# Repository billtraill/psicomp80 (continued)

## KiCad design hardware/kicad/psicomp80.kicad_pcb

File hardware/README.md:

# PSI COMP 80 main board drawings

Vector drawings of the Powertran kit's main board, and a routed KiCad board. The board
gets its parts and positions from the photos of the kit sheets in `info/pictures/`
(`kit-component-layout.webp` and `kit-pcb-artwork.webp`). It gets its electrical
connections from the circuit diagrams in the Wireless World articles.

| File | What it is |
|---|---|
| `psicomp80_pcb_routed.svg` | **The electrically accurate artwork.** The board routed from the netlist transcribed from the article circuit diagrams, drawn like the kit sheet and seen from the component side: blue is the component (top) side, red the solder (bottom) side. |
| `psicomp80_component_layout.svg` | The component layout sheet, redrawn: board outline, section boundaries, every IC with its number and type, the discrete parts as drawn on the kit sheet, and the keyboard legends. |
| `psicomp80_pcb_artwork.svg` | The kit's original copper artwork, traced from the photo (approximate), with the pads and legends redrawn on top. |
| `kicad/psicomp80.kicad_pro`, `kicad/psicomp80.kicad_pcb` | A KiCad 10 project. Every part sits on a standard footprint with its nets, and the board is routed on two layers. The traced original copper stays on two user layers, **Artwork.Blue.Top** and **Artwork.Red.Bottom**, for comparison. |
| `kicad/PSI_COMP80.pretty`, `kicad/fp-lib-table` | The project library: the two-pad key switch footprint and the wiring-pad footprints. |
| `tools/netlist/` | The netlist, one file per article figure, plus the merged `psicomp80_netlist.json`. Its README covers sources, conventions and the points where a figure had to be interpreted. |
| `../hardware.html` | A web page of the board: zoom and pan, each side's copper on and off (routed or traced kit artwork), click a part or track for its pins and signal, the circuits talked through, and the parts list. `tools/make_hardware_page.py` makes it from the KiCad board and the netlist, with `tools/hardware_template.html`; it needs only Python 3. |

The board is 16 in × 12 in between the crop marks on the artwork. The scale comes from
the 0.1 in DIP pad pitch. The board is double-sided. On the kit's artwork the "1" mark
and the "COMPONENT SIDE" legend are printed in blue, and the "2" mark is red and reads
mirrored. So blue is the component side and red the solder side.

## How accurate it is

- **Connections** follow the article circuit diagrams pin by pin. Some figures don't
  print every pin number, and the keyboard encoder isn't drawn at all; the netlist
  README lists each case.
- **The routed tracks are not the original tracks.** Electrically they match the
  article, but the track paths don't follow the 1979 artwork. The 21L02 RAM columns are
  the exception: `make_kicad.py` pre-routes their buses itself on the component side,
  the way the original artwork does, and Freerouting routes everything else.
- **Design checks.** KiCad's DRC on the routed board finds 0 unconnected pads, and no
  clearance violations or shorts. Tracks are 0.25 mm with 0.2 mm clearance; power nets
  are 0.6 mm. Freerouting necks a few tracks down to 0.125–0.19 mm between pads. The
  remaining DRC messages are cosmetic: silkscreen overlaps, and courtyard overlaps
  where the kit sheet packs parts tightly. The "library not included" warnings go away
  once KiCad's default footprint libraries are set up.
- **IC positions** match the kit sheet. The two photos register onto each other to
  within a few hundredths of an inch, and every IC is snapped to the 0.1 in grid. IC
  types follow the article where the photo was hard to read; see `NOTES` in
  `tools/board_data.py`.
- **Discrete parts** sit at their kit-sheet position when the kit sheet shows the same
  reference, such as R40, C14, TR9 or VR1. Otherwise they go in the nearest free spot,
  in their own section of the board, to the pins they connect to.
- **The traced original copper** is approximate. The artwork photo only resolves about
  65 pixels per inch, so where tracks run close together they merge. A flat 600 dpi
  scan of the artwork sheet would make it close to track-accurate: change the corners
  in `tools/trace_artwork.py` and re-run it.

## The expansion plug

The articles never print J1's pinout, so `tools/netlist/net_board.json` gives it one. Odd pins
are the row nearer the middle of the board.

| Pins | Signals |
|---|---|
| 2, 21, 22, 31, 32, 47, 48 | 0 V |
| 4, 63, 64 | +5 V |
| 5–20 | A0–A15, straight from the Z80 |
| 23–30 | D0–D7, the buffered side of IC9–IC12 |
| 33–46 | RD, WR, MREQ, IORQ, M1, RFSH, MEM_MREQ (the IC17 side of LK3), HALT, WAIT/BUSRQ, BUSAK, INT, NMI, RESET, 2 MHz clock |
| 49–54 | IC2's spare outputs: OUT 00, 80, 40, C0, A0, E0 |
| 55–59 | IC3's spare outputs: IN 04, 02, 06, 05, 07 |
| 60, 61, 62 | +12 V, −5 V, −12 V |
| 1, 3 | not connected |

`tools/wire_expansion.py` put these nets on the routed board, and `route_board.py --keep`
routed them without disturbing the tracks already there. `tools/finish_routes.py` routed
the last six, which Freerouting couldn't fit, on a 0.1–0.2 mm grid.

## Regenerating

The scripts are in `tools/`:

| Step | Script | Runs under |
|---|---|---|
| 1 | `merge_netlist.py`: merges `netlist/net_*.json` and reports dangling nets | any Python 3 |
| 2 | `make_kicad.py`: builds the board, placing parts and putting nets on pads | KiCad's Python |
| 3 | `route_board.py`: routes the board with Freerouting (needs Java) | KiCad's Python |
| 4 | `export_routed_svg.py`: writes `psicomp80_pcb_routed.svg` | KiCad's Python |
| – | `make_drawings.py`: writes the component layout and traced artwork SVGs | any Python 3 |
| – | `trace_artwork.py`: traces the copper out of the photo (only if the photo changes) | numpy, OpenCV, Pillow, potrace |

`board_data.py` holds every placement read from the photos. Edit it to move a part.

```bash
cd hardware/tools && python3 merge_netlist.py
```

```bash
cd hardware/tools && /Applications/KiCad/KiCad.app/Contents/Frameworks/Python.framework/Versions/Current/bin/python3 make_kicad.py
```

```bash
cd hardware/tools && /Applications/KiCad/KiCad.app/Contents/Frameworks/Python.framework/Versions/Current/bin/python3 route_board.py --freerouting freerouting-2.5.0.jar --java /opt/homebrew/opt/openjdk/bin/java
```

```bash
cd hardware/tools && /Applications/KiCad/KiCad.app/Contents/Frameworks/Python.framework/Versions/Current/bin/python3 export_routed_svg.py
```

To route only what's new, keeping the existing tracks, add `--keep` to `route_board.py`; then
route anything left over with the grid router:

```bash
cd hardware/tools && /Applications/KiCad/KiCad.app/Contents/Frameworks/Python.framework/Versions/Current/bin/python3 finish_routes.py
```

Freerouting comes from https://github.com/freerouting/freerouting/releases, and Java
from `brew install openjdk`.

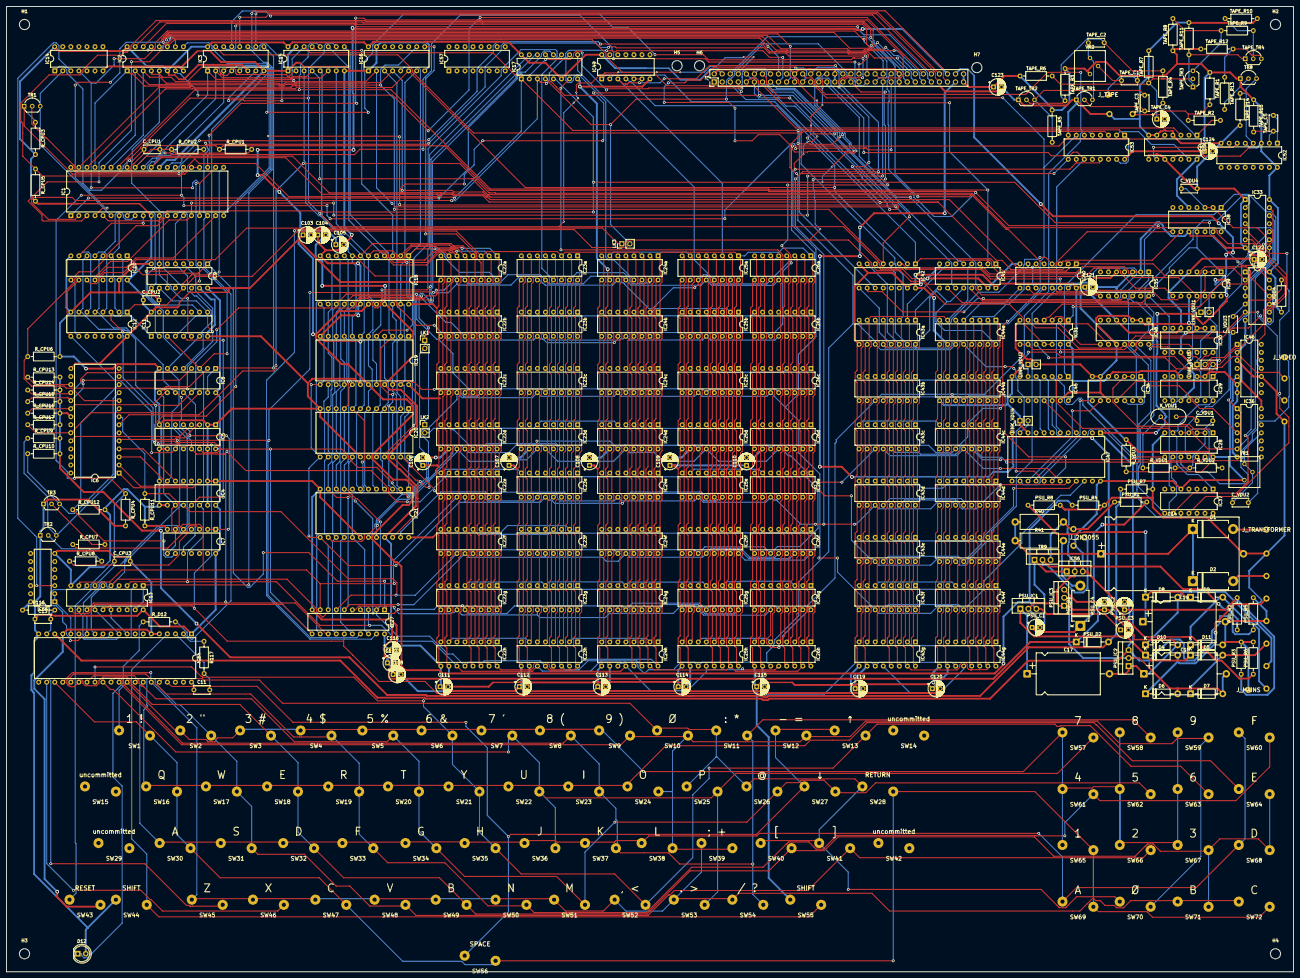
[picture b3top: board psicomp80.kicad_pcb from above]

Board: 2 copper layers, 406.4 x 304.8 mm, 316 parts (0 on the bottom side), 269 nets.

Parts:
C11: 56p; C_Disc_D5.0mm_W2.5mm_P5.00mm
C13: 22n; C_Disc_D5.0mm_W2.5mm_P5.00mm
C14: 4700u 25V; CP_Axial_L42.0mm_D23.0mm_P45.00mm_Horizontal
C17, C18: 1000u 25V; CP_Axial_L20.0mm_D13.0mm_P26.00mm_Horizontal
C19: 220u 100V; CP_Axial_L20.0mm_D13.0mm_P26.00mm_Horizontal
C103, C104, C105, C106, C107, C108, C109, C110, C111, C112, C113, C114, C115, C116, C117, C118: 100n tantalum; CP_Radial_D5.0mm_P2.50mm
C119, C120, C121, C122, C123, C124: 1u; CP_Radial_D5.0mm_P2.50mm
C_CPU1: 33p; C_Disc_D5.0mm_W2.5mm_P5.00mm
C_CPU2, C_CPU3: 100n; C_Disc_D5.0mm_W2.5mm_P5.00mm
C_VDU1: 22p; C_Disc_D5.0mm_W2.5mm_P5.00mm
C_VDU2: 220n; C_Disc_D5.0mm_W2.5mm_P5.00mm
C_VDU3: 100n; C_Disc_D5.0mm_W2.5mm_P5.00mm
C_VDU4: 200p; C_Disc_D5.0mm_W2.5mm_P5.00mm
D1, D2: 1N5401; D_DO-201AD_P12.70mm_Horizontal
D4, D5, D6, D7, D8, D9, D10, D11: 1N4002; D_DO-41_SOD81_P10.16mm_Horizontal
D12: LED (TIL209 in article); LED_D5.0mm
H1, H2, H3, H4, H5, H6, H7: MountingHole; MountingHole_3.2mm_M3
IC1: Z80; DIP-40_W15.24mm
IC2, IC3, IC17: 74LS138; DIP-16_W7.62mm
IC4, IC5: 74C173; DIP-16_W7.62mm
IC6: MM57109; DIP-28_W15.24mm
IC7: 4011; DIP-14_W7.62mm
IC8, IC9, IC10, IC11, IC12, IC15, IC16, IC53: 74LS367; DIP-16_W7.62mm
IC13, IC27: 81LS95; DIP-20_W7.62mm
IC14, IC28: 74LS04; DIP-14_W7.62mm
IC18, IC19, IC20, IC21: 2708; DIP-24_W15.24mm
IC22a, IC22b, IC22c, IC22d, IC22e, IC22f, IC22g, IC22h, IC23a, IC23b, IC23c, IC23d, IC23e, IC23f, IC23g, IC23h, IC24a, IC24b, IC24c, IC24d, IC24e, IC24f, IC24g, IC24h, IC25a, IC25b, IC25c, IC25d, IC25e, IC25f, IC25g, IC25h, IC26a, IC26b, IC26c, IC26d, IC26e, IC26f, IC26g, IC26h, IC43a, IC43b, IC43c, IC43d, IC43e, IC43f, IC43g, IC44a, IC44b, IC44c, IC44d, IC44e, IC44f, IC44g: 21L02; DIP-16_W7.62mm
IC29, IC30, IC35, IC38, IC39, IC48: 7493; DIP-14_W7.62mm
IC31, IC49: 74LS02; DIP-14_W7.62mm
IC32, IC55: 74LS00; DIP-14_W7.62mm
IC33: 7425; DIP-14_W7.62mm
IC34, IC46: 7490; DIP-14_W7.62mm
IC36: 74121; DIP-14_W7.62mm
IC37: 7492; DIP-14_W7.62mm
IC40, IC41, IC42: 74LS157; DIP-16_W7.62mm
IC45: 74165; DIP-16_W7.62mm
IC47: 2513; DIP-24_W15.24mm
IC51: 4013; DIP-14_W7.62mm
IC52: 4528; DIP-16_W7.62mm
IC54: AY-5-2376; DIP-40_W15.24mm
IC56: 7805; TO-220-3_Vertical
IC57: 74LS139; DIP-16_W7.62mm
J1: EXPANSION PLUG; PinHeader_2x32_P2.54mm_Vertical
J_2N3055: 2N3055 on heatsink (off-board); Pads_2N3055
J_MAINS: mains input (off-board); Pads_MAINS
J_TAPE: tape connections; Pads_TAPE
J_TRANSFORMER: mains transformer secondaries (off-board); Pads_TRANSFORMER
J_VIDEO: video / sync output pads; Pads_VIDEO
LINK_VDU1: Link; PinHeader_1x02_P2.54mm_Vertical
LINK_VDU2, LINK_VDU4: link (fitted for ASCII); PinHeader_1x02_P2.54mm_Vertical
LINK_VDU3: link: IC29 pin 12 or pin 14; PinHeader_1x03_P2.54mm_Vertical
LK1: wire link (normally NOT fitted); PinHeader_1x02_P2.54mm_Vertical
LK2, LK3: wire link (normally fitted); PinHeader_1x02_P2.54mm_Vertical
PSU_C1: 8u; CP_Radial_D5.0mm_P2.50mm
PSU_C2: 4u7 tantalum; CP_Radial_D5.0mm_P2.50mm
PSU_C3, PSU_C4: 1u tantalum; CP_Radial_D5.0mm_P2.50mm
PSU_D1: 1N5401; D_DO-201AD_P12.70mm_Horizontal
PSU_D2: 1N4001; D_DO-41_SOD81_P10.16mm_Horizontal
PSU_IC1: 7812; TO-220-3_Vertical
PSU_IC2: 7912; TO-220-3_Vertical
PSU_IC3: 7905; TO-220-3_Vertical
PSU_R1, PSU_R2: 100; R_Axial_DIN0207_L6.3mm_D2.5mm_P10.16mm_Horizontal
PSU_R3, PSU_R4, PSU_R5, PSU_R6, PSU_R7: 1k; R_Axial_DIN0207_L6.3mm_D2.5mm_P10.16mm_Horizontal
PSU_R8: 4k7; R_Axial_DIN0207_L6.3mm_D2.5mm_P10.16mm_Horizontal
R40: 0R22; R_Axial_DIN0414_L11.9mm_D4.5mm_P15.24mm_Horizontal
R41: 0R56; R_Axial_DIN0414_L11.9mm_D4.5mm_P15.24mm_Horizontal
R116: 680k (datasheet; kit label unreadable, possibly "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; R_Axial_DIN0207_L6.3mm_D2.5mm_P10.16mm_Horizontal
R117: ? (datasheet 100k; ~47-56k would give ~50kHz with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; R_Axial_DIN0207_L6.3mm_D2.5mm_P10.16mm_Horizontal
R_CPU1: 220; R_Axial_DIN0207_L6.3mm_D2.5mm_P10.16mm_Horizontal
R_CPU2: 1k2; R_Axial_DIN0207_L6.3mm_D2.5mm_P10.16mm_Horizontal
R_CPU3: 10R; R_Axial_DIN0207_L6.3mm_D2.5mm_P10.16mm_Horizontal
R_CPU4, R_CPU5, R_CPU7, R_CPU8, R_CPU9, R_CPU10: 47k; R_Axial_DIN0207_L6.3mm_D2.5mm_P10.16mm_Horizontal
R_CPU6, R_CPU11, R_CPU12, R_CPU13, R_CPU14, R_CPU15, R_CPU16, R_CPU17: 10k; R_Axial_DIN0207_L6.3mm_D2.5mm_P10.16mm_Horizontal
R_D12: 560R; R_Axial_DIN0207_L6.3mm_D2.5mm_P10.16mm_Horizontal
R_VDU1, R_VDU2: 470; R_Axial_DIN0207_L6.3mm_D2.5mm_P10.16mm_Horizontal
R_VDU3: 10k; R_Axial_DIN0207_L6.3mm_D2.5mm_P10.16mm_Horizontal
R_VDU4: 2k7; R_Axial_DIN0207_L6.3mm_D2.5mm_P10.16mm_Horizontal
SW1: 1 !; KeySwitch_2pad
SW2: 2 "; KeySwitch_2pad
SW3: 3 #; KeySwitch_2pad
SW4: 4 $; KeySwitch_2pad
SW5: 5 %; KeySwitch_2pad
SW6: 6 &; KeySwitch_2pad
SW7: 7 '; KeySwitch_2pad
SW8: 8 (; KeySwitch_2pad
SW9: 9 ); KeySwitch_2pad
SW10, SW70: Ø; KeySwitch_2pad
SW11: : *; KeySwitch_2pad
SW12: - =; KeySwitch_2pad
SW13: ↑; KeySwitch_2pad
SW14, SW15, SW29, SW42: uncommitted; KeySwitch_2pad
SW16: Q; KeySwitch_2pad
SW17: W; KeySwitch_2pad
SW18, SW64: E; KeySwitch_2pad
SW19: R; KeySwitch_2pad
SW20: T; KeySwitch_2pad
SW21: Y; KeySwitch_2pad
SW22: U; KeySwitch_2pad
SW23: I; KeySwitch_2pad
SW24: O; KeySwitch_2pad
SW25: P; KeySwitch_2pad
SW26: @; KeySwitch_2pad
SW27: ↓; KeySwitch_2pad
SW28: RETURN; KeySwitch_2pad
SW30, SW69: A; KeySwitch_2pad
SW31: S; KeySwitch_2pad
SW32, SW68: D; KeySwitch_2pad
SW33, SW60: F; KeySwitch_2pad
SW34: G; KeySwitch_2pad
SW35: H; KeySwitch_2pad
SW36: J; KeySwitch_2pad
SW37: K; KeySwitch_2pad
SW38: L; KeySwitch_2pad
SW39: ; +; KeySwitch_2pad
SW40: [; KeySwitch_2pad
SW41: ]; KeySwitch_2pad
SW43: RESET; KeySwitch_2pad
SW44, SW55: SHIFT; KeySwitch_2pad
SW45: Z; KeySwitch_2pad
SW46: X; KeySwitch_2pad
SW47, SW72: C; KeySwitch_2pad
SW48: V; KeySwitch_2pad
SW49, SW71: B; KeySwitch_2pad
SW50: N; KeySwitch_2pad
SW51: M; KeySwitch_2pad
SW52: , <; KeySwitch_2pad
SW53: . >; KeySwitch_2pad
SW54: / ?; KeySwitch_2pad
SW56: SPACE; KeySwitch_2pad
SW57: 7; KeySwitch_2pad
SW58: 8; KeySwitch_2pad
SW59: 9; KeySwitch_2pad
SW61: 4; KeySwitch_2pad
SW62: 5; KeySwitch_2pad
SW63: 6; KeySwitch_2pad
SW65: 1; KeySwitch_2pad
SW66: 2; KeySwitch_2pad
SW67: 3; KeySwitch_2pad
TAPE_C1, TAPE_C5: 100n; C_Disc_D5.0mm_W2.5mm_P5.00mm
TAPE_C2, TAPE_C3: 10n; C_Disc_D5.0mm_W2.5mm_P5.00mm
TAPE_C4: 10u; CP_Radial_D5.0mm_P2.50mm
TAPE_R1, TAPE_R3: 75k; R_Axial_DIN0207_L6.3mm_D2.5mm_P10.16mm_Horizontal
TAPE_R2, TAPE_R4: 56k; R_Axial_DIN0207_L6.3mm_D2.5mm_P10.16mm_Horizontal
TAPE_R5, TAPE_R9, TAPE_R10: 4k7; R_Axial_DIN0207_L6.3mm_D2.5mm_P10.16mm_Horizontal
TAPE_R6, TAPE_R7: 6k8; R_Axial_DIN0207_L6.3mm_D2.5mm_P10.16mm_Horizontal
TAPE_R8: 220; R_Axial_DIN0207_L6.3mm_D2.5mm_P10.16mm_Horizontal
TAPE_R11: 2k2; R_Axial_DIN0207_L6.3mm_D2.5mm_P10.16mm_Horizontal
TAPE_R12, TAPE_R13, TAPE_R14: 1k; R_Axial_DIN0207_L6.3mm_D2.5mm_P10.16mm_Horizontal
TAPE_R15: 27k; R_Axial_DIN0207_L6.3mm_D2.5mm_P10.16mm_Horizontal
TAPE_TR1, TAPE_TR2, TAPE_TR3, TAPE_TR4: 2N3904; TO-92_Inline_Wide
TR1, TR2, TR3, TR8: 2N3906; TO-92_Inline_Wide
TR9: TIP30; TO-220-3_Vertical
VR1: 20k multiturn; Potentiometer_Bourns_3386P_Vertical
VR2: 5k preset; Potentiometer_Bourns_3386P_Vertical
X_VDU1: 8MHz crystal; Crystal_HC49-U_Vertical

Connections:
+5V: C13.1, C103.1, C106.1, C107.1, C108.1, C109.1, C110.1, C111.1, C112.1, C113.1, C114.1, C115.1, C116.1, C119.1, C120.1, C121.1, C122.1, C123.1, C124.1, C_CPU2.1, D12.2, IC1.11, IC2.6, IC2.16, IC3.6, IC3.16, IC4.16, IC5.16, IC6.15, IC7.14, IC8.16, IC9.16, IC10.16, IC11.16, IC12.16, IC13.20, IC14.14, IC15.16, IC16.16, IC17.6, IC17.16, IC18.24, IC19.24, IC20.24, IC21.24, IC22a.9, IC22b.9, IC22c.9, IC22d.9, IC22e.9, IC22f.9, IC22g.9, IC22h.9, IC23a.9, IC23b.9, IC23c.9, IC23d.9, IC23e.9, IC23f.9, IC23g.9, IC23h.9, IC24a.9, IC24b.9, IC24c.9, IC24d.9, IC24e.9, IC24f.9, IC24g.9, IC24h.9, IC25a.9, IC25b.9, IC25c.9, IC25d.9, IC25e.9, IC25f.9, IC25g.9, IC25h.9, IC26a.9, IC26b.9, IC26c.9, IC26d.9, IC26e.9, IC26f.9, IC26g.9, IC26h.9, IC27.20, IC28.14, IC29.5, IC30.5, IC31.14, IC32.14, IC33.14, IC34.5, IC35.5, IC36.14, IC37.5, IC38.5, IC39.5, IC40.16, IC41.16, IC42.16, IC43a.10, IC43b.10, IC43c.10, IC43d.10, IC43e.10, IC43f.10, IC43g.10, IC44a.10, IC44b.10, IC44c.10, IC44d.10, IC44e.10, IC44f.10, IC44g.10, IC45.16, IC46.5, IC47.24, IC48.5, IC49.14, IC51.14, IC52.3, IC52.5, IC52.16, IC53.16, IC54.1, IC54.20, IC55.14, IC56.3, J1.4, J1.63, J1.64, J_2N3055.E, PSU_C2.1, PSU_R2.2, PSU_R3.1, R116.1, R_CPU3.2, R_CPU4.2, R_CPU5.2, R_VDU3.1, R_VDU4.1, SW44.1, SW55.1, TAPE_R1.1, TAPE_R3.1, TAPE_R5.1, TAPE_R6.1, TAPE_R8.1, TAPE_R12.1, TAPE_R15.1, TR2.1, TR3.1, TR8.1, VR1.1, VR2.1
+12V: C105.1, C118.1, IC18.19, IC19.19, IC20.19, IC21.19, J1.60, PSU_C3.1, PSU_IC1.3, PSU_R4.1
-4_5V: IC6.21, PSU_D2.2, PSU_R7.1, R_CPU9.2, R_CPU10.2, R_CPU13.2, R_CPU14.2, R_CPU15.2, R_CPU16.2, R_CPU17.2
-5V: C104.2, C117.2, IC18.21, IC19.21, IC20.21, IC21.21, IC47.12, J1.61, PSU_C4.2, PSU_D2.1, PSU_IC3.3, PSU_R6.1
-12V: IC47.1, IC54.18, J1.62, PSU_IC2.3, PSU_R5.1
A0: IC1.30, IC3.3, IC15.2, IC40.2, J1.5
A1: IC1.31, IC3.2, IC15.4, IC40.5, J1.6
A2: IC1.32, IC3.1, IC15.6, IC40.11, J1.7
A3: IC1.33, IC15.10, IC40.14, J1.8
A4: IC1.34, IC15.12, IC41.2, J1.9
A5: IC1.35, IC2.3, IC15.14, IC41.5, J1.10
A6: IC1.36, IC2.2, IC16.2, IC41.11, J1.11
A7: IC1.37, IC2.1, IC16.4, IC41.14, J1.12
A8: IC1.38, IC16.6, IC42.2, J1.13
A9: IC1.39, IC16.10, IC42.5, J1.14
A10: IC1.40, IC17.1, IC42.11, J1.15
A11: IC1.1, IC17.2, J1.16
A12: IC1.2, IC17.3, J1.17
A13: IC1.3, J1.18
A14: IC1.4, J1.19
A15: IC1.5, IC17.5, IC32.13, J1.20
BUSAK_N: IC1.23, J1.42
CLK: IC1.6, IC14.2, TR1.3
CLK_2MHZ: C_CPU1.1, IC14.1, IC30.9, J1.46, R_CPU1.1
CPU_HOLD_DRV_N: IC7.4, R_CPU8.1
CPU_IC2_Y0: IC2.15, J1.49
CPU_IC2_Y1: IC2.14, J1.50
CPU_IC2_Y2: IC2.13, J1.51
CPU_IC2_Y3: IC2.12, J1.52
CPU_IC2_Y4: IC2.11, IC51.3
CPU_IC2_Y5: IC2.10, J1.53
CPU_IC2_Y6: IC2.9, IC4.7, IC5.7
CPU_IC2_Y7: IC2.7, J1.54
CPU_IC3_Y0: IC3.15, IC53.1, IC53.15
CPU_IC3_Y1: IC3.14, J1.55
CPU_IC3_Y2: IC3.13, J1.56
CPU_IC3_Y3: IC3.12, J1.57
CPU_IC3_Y4: IC3.11, IC13.1, IC13.19
CPU_IC3_Y5: IC3.10, J1.58
CPU_IC3_Y6: IC3.9, IC8.1, IC8.15
CPU_IC3_Y7: IC3.7, J1.59
CPU_LATCH_HOLD: IC5.6, IC7.5
CPU_LATCH_POR: IC5.5, IC7.1, IC7.2
CPU_MM_BR: IC6.23, IC8.14, R_CPU17.1
CPU_MM_DO1: IC6.17, IC8.2, R_CPU13.1
CPU_MM_DO2: IC6.18, IC8.4, R_CPU14.1
CPU_MM_DO3: IC6.19, IC8.6, R_CPU15.1
CPU_MM_DO4: IC6.20, IC8.10, R_CPU16.1
CPU_MM_HOLD: IC6.9, R_CPU9.1, TR2.3
CPU_MM_I1: IC4.3, IC6.1
CPU_MM_I2: IC4.4, IC6.2
CPU_MM_I3: IC4.5, IC6.3
CPU_MM_I4: IC4.6, IC6.4
CPU_MM_I5: IC5.3, IC6.5
CPU_MM_I6: IC5.4, IC6.24
CPU_MM_ISEL: IC6.8, IC7.6, IC7.8, R_CPU11.1
CPU_MM_POR: IC6.11, R_CPU10.1, TR3.3
CPU_MM_RDY: IC6.12, IC7.9, R_CPU12.1
CPU_MM_RDY_GATED_N: IC7.10, IC8.12
CPU_POR_DRV_N: IC7.3, R_CPU7.1
CPU_TR1_B: C_CPU1.2, R_CPU1.2, R_CPU2.1, TR1.2
CPU_TR1_E: R_CPU2.2, R_CPU3.1, TR1.1
CPU_TR2_B: R_CPU8.2, TR2.2
CPU_TR3_B: R_CPU7.2, TR3.2
CPU_ZD0: IC1.14, IC9.3, IC11.2
CPU_ZD1: IC1.15, IC9.5, IC11.4
CPU_ZD2: IC1.12, IC9.7, IC11.6
CPU_ZD3: IC1.8, IC9.9, IC11.10
CPU_ZD4: IC1.7, IC10.3, IC12.2
CPU_ZD5: IC1.9, IC10.5, IC12.4
CPU_ZD6: IC1.10, IC10.7, IC12.6
CPU_ZD7: IC1.13, IC10.9, IC12.10
CPU_Z_MREQ_N: IC1.19, IC10.12
CPU_Z_RD_N: IC1.21, IC9.12
CPU_Z_WR_N: IC1.22, IC9.14
D0: IC4.14, IC8.3, IC9.2, IC11.3, IC13.3, IC22h.11, IC23h.11, IC24h.11, IC25h.11, IC26h.11, IC27.3, IC43a.11, IC44a.11, IC53.3, J1.23
D1: IC4.13, IC8.5, IC9.4, IC11.5, IC13.5, IC22g.11, IC23g.11, IC24g.11, IC25g.11, IC26g.11, IC27.5, IC43b.11, IC44b.11, IC53.5, J1.24
D2: IC4.12, IC8.7, IC9.6, IC11.7, IC13.7, IC22f.11, IC23f.11, IC24f.11, IC25f.11, IC26f.11, IC27.7, IC43c.11, IC44c.11, IC53.7, J1.25
D3: IC4.11, IC8.9, IC9.10, IC11.9, IC13.9, IC22e.11, IC23e.11, IC24e.11, IC25e.11, IC26e.11, IC27.9, IC43d.11, IC44d.11, IC53.9, J1.26
D4: IC5.14, IC10.2, IC12.3, IC13.11, IC22d.11, IC23d.11, IC24d.11, IC25d.11, IC26d.11, IC27.11, IC43e.11, IC44e.11, IC53.11, J1.27
D5: IC5.13, IC8.11, IC10.4, IC12.5, IC13.13, IC22c.11, IC23c.11, IC24c.11, IC25c.11, IC26c.11, IC27.13, IC43f.11, IC44f.11, IC53.13, J1.28
D6: IC5.12, IC8.13, IC10.6, IC12.7, IC13.15, IC22b.11, IC23b.11, IC24b.11, IC25b.11, IC26b.11, IC27.15, IC43g.11, IC44g.11, J1.29
D7: IC5.11, IC10.10, IC12.9, IC22a.11, IC23a.11, IC24a.11, IC25a.11, IC26a.11, IC27.17, IC51.5, J1.30
GND: C14.2, C17.2, C18.1, C19.2, C103.2, C104.1, C105.2, C106.2, C107.2, C108.2, C109.2, C110.2, C111.2, C112.2, C113.2, C114.2, C115.2, C116.2, C117.1, C118.2, C119.2, C120.2, C121.2, C122.2, C123.2, C124.2, C_CPU2.2, C_CPU3.2, C_VDU4.2, D10.2, D11.2, IC1.29, IC2.8, IC3.8, IC4.1, IC4.2, IC4.8, IC4.9, IC4.10, IC4.15, IC5.1, IC5.2, IC5.8, IC5.9, IC5.10, IC5.15, IC7.7, IC8.8, IC9.8, IC9.15, IC10.8, IC10.15, IC11.8, IC12.8, IC13.10, IC14.7, IC15.1, IC15.8, IC15.15, IC16.1, IC16.8, IC16.15, IC17.8, IC18.12, IC18.18, IC19.12, IC19.18, IC20.12, IC20.18, IC21.12, IC21.18, IC22a.10, IC22b.10, IC22c.10, IC22d.10, IC22e.10, IC22f.10, IC22g.10, IC22h.10, IC23a.10, IC23b.10, IC23c.10, IC23d.10, IC23e.10, IC23f.10, IC23g.10, IC23h.10, IC24a.10, IC24b.10, IC24c.10, IC24d.10, IC24e.10, IC24f.10, IC24g.10, IC24h.10, IC25a.10, IC25b.10, IC25c.10, IC25d.10, IC25e.10, IC25f.10, IC25g.10, IC25h.10, IC26a.10, IC26b.10, IC26c.10, IC26d.10, IC26e.10, IC26f.10, IC26g.10, IC26h.10, IC27.10, IC28.7, IC29.2, IC29.3, IC29.10, IC30.2, IC30.3, IC30.10, IC31.7, IC32.7, IC33.1, IC33.7, IC34.6, IC34.7, IC34.10, IC35.2, IC35.3, IC35.10, IC36.7, IC37.10, IC38.10, IC39.10, IC40.8, IC40.15, IC41.8, IC41.15, IC42.8, IC42.15, IC43a.9, IC43b.9, IC43c.9, IC43d.9, IC43e.9, IC43f.9, IC43g.9, IC44a.9, IC44b.9, IC44c.9, IC44d.9, IC44e.9, IC44f.9, IC44g.9, IC45.8, IC45.15, IC46.2, IC46.3, IC46.6, IC46.7, IC46.10, IC47.10, IC48.2, IC48.3, IC48.10, IC49.7, IC51.4, IC51.6, IC51.7, IC51.8, IC51.10, IC52.8, IC53.8, IC54.5, IC54.6, IC54.17, IC55.7, IC56.2, J1.2, J1.21, J1.22, J1.31, J1.32, J1.47, J1.48, J_MAINS.E, J_TAPE.GND, J_TRANSFORMER.S1_CT, J_TRANSFORMER.S2_CT, J_VIDEO.GND, LINK_VDU2.2, LINK_VDU4.1, PSU_C1.2, PSU_C2.2, PSU_C3.2, PSU_C4.1, PSU_IC1.2, PSU_IC2.1, PSU_IC3.1, PSU_R3.2, PSU_R4.2, PSU_R5.2, PSU_R6.2, PSU_R7.2, PSU_R8.2, R_CPU6.2, R_CPU11.2, R_CPU12.2, SW43.2, TAPE_R7.2, TAPE_R10.2, TAPE_R11.2, TAPE_R14.2, TAPE_TR1.1, TAPE_TR2.1
HALT_N: IC1.18, J1.40, R_D12.2
INT_N: IC1.16, IC6.10, J1.43, R_CPU6.1
IORQ_N: IC1.20, IC2.4, IC3.4, J1.36
KBD_D0: IC13.2, IC54.15
KBD_D1: IC13.4, IC54.14
KBD_D2: IC13.6, IC54.13
KBD_D3: IC13.8, IC54.12
KBD_D4: IC13.12, IC54.11
KBD_D5: IC13.14, IC54.10
KBD_D6: IC13.16, IC54.9
KBD_LED_K: D12.1, R_D12.1
KBD_OSC_A: C11.1, IC54.40
KBD_OSC_B: IC54.2, R117.1
KBD_OSC_C: C11.2, IC54.3, R117.2
KBD_SHIFT: IC54.4, SW44.2, SW55.2
KBD_STB_DELAY: C13.2, IC54.19, R116.2
KBD_STROBE: IC14.3, IC55.3
KBD_STROBE_N: IC54.16, IC55.1, IC55.2
KBD_X2: IC54.37, SW12.1, SW13.1, SW27.1, SW56.1
KBD_X3: IC54.36, SW10.1, SW11.1, SW25.1, SW26.1, SW28.1, SW40.1, SW41.1, SW70.1
KBD_X4: IC54.35, SW39.1, SW45.1, SW46.1, SW47.1, SW48.1, SW49.1, SW50.1, SW51.1, SW52.1, SW53.1, SW54.1, SW71.1, SW72.1
KBD_X5: IC54.34, SW30.1, SW31.1, SW32.1, SW33.1, SW34.1, SW35.1, SW36.1, SW37.1, SW38.1, SW60.1, SW68.1, SW69.1
KBD_X6: IC54.33, SW16.1, SW17.1, SW18.1, SW19.1, SW20.1, SW21.1, SW22.1, SW23.1, SW24.1, SW64.1
KBD_X7: IC54.32, SW1.1, SW2.1, SW3.1, SW4.1, SW5.1, SW6.1, SW7.1, SW8.1, SW9.1, SW57.1, SW58.1, SW59.1, SW61.1, SW62.1, SW63.1, SW65.1, SW66.1, SW67.1
KBD_Y0: IC54.31, SW9.2, SW10.2, SW12.2, SW24.2, SW38.2, SW39.2, SW59.2, SW70.2
KBD_Y1: IC54.30, SW8.2, SW11.2, SW23.2, SW37.2, SW54.2, SW58.2
KBD_Y2: IC54.29, SW7.2, SW22.2, SW25.2, SW36.2, SW53.2, SW57.2
KBD_Y3: IC54.28, SW6.2, SW13.2, SW21.2, SW35.2, SW52.2, SW63.2
KBD_Y4: IC54.27, SW5.2, SW20.2, SW26.2, SW27.2, SW34.2, SW51.2, SW62.2
KBD_Y5: IC54.26, SW4.2, SW19.2, SW33.2, SW50.2, SW60.2, SW61.2
KBD_Y6: IC54.25, SW3.2, SW18.2, SW32.2, SW40.2, SW49.2, SW64.2, SW67.2, SW68.2, SW71.2
KBD_Y7: IC54.24, SW2.2, SW17.2, SW31.2, SW41.2, SW48.2, SW66.2
KBD_Y8: IC54.23, SW1.2, SW16.2, SW28.2, SW30.2, SW47.2, SW56.2, SW65.2, SW69.2, SW72.2
KBD_Y9: IC54.22, SW46.2
KBD_Y10: IC54.21, SW45.2
M1_N: IC1.27, J1.37
MEM_BA0: IC15.3, IC18.8, IC19.8, IC20.8, IC21.8, IC22a.8, IC22b.8, IC22c.8, IC22d.8, IC22e.8, IC22f.8, IC22g.8, IC22h.8, IC23a.8, IC23b.8, IC23c.8, IC23d.8, IC23e.8, IC23f.8, IC23g.8, IC23h.8, IC24a.8, IC24b.8, IC24c.8, IC24d.8, IC24e.8, IC24f.8, IC24g.8, IC24h.8, IC25a.8, IC25b.8, IC25c.8, IC25d.8, IC25e.8, IC25f.8, IC25g.8, IC25h.8, IC26a.8, IC26b.8, IC26c.8, IC26d.8, IC26e.8, IC26f.8, IC26g.8, IC26h.8
MEM_BA1: IC15.5, IC18.7, IC19.7, IC20.7, IC21.7, IC22a.4, IC22b.4, IC22c.4, IC22d.4, IC22e.4, IC22f.4, IC22g.4, IC22h.4, IC23a.4, IC23b.4, IC23c.4, IC23d.4, IC23e.4, IC23f.4, IC23g.4, IC23h.4, IC24a.4, IC24b.4, IC24c.4, IC24d.4, IC24e.4, IC24f.4, IC24g.4, IC24h.4, IC25a.4, IC25b.4, IC25c.4, IC25d.4, IC25e.4, IC25f.4, IC25g.4, IC25h.4, IC26a.4, IC26b.4, IC26c.4, IC26d.4, IC26e.4, IC26f.4, IC26g.4, IC26h.4
MEM_BA2: IC15.7, IC18.6, IC19.6, IC20.6, IC21.6, IC22a.5, IC22b.5, IC22c.5, IC22d.5, IC22e.5, IC22f.5, IC22g.5, IC22h.5, IC23a.5, IC23b.5, IC23c.5, IC23d.5, IC23e.5, IC23f.5, IC23g.5, IC23h.5, IC24a.5, IC24b.5, IC24c.5, IC24d.5, IC24e.5, IC24f.5, IC24g.5, IC24h.5, IC25a.5, IC25b.5, IC25c.5, IC25d.5, IC25e.5, IC25f.5, IC25g.5, IC25h.5, IC26a.5, IC26b.5, IC26c.5, IC26d.5, IC26e.5, IC26f.5, IC26g.5, IC26h.5
MEM_BA3: IC15.9, IC18.5, IC19.5, IC20.5, IC21.5, IC22a.6, IC22b.6, IC22c.6, IC22d.6, IC22e.6, IC22f.6, IC22g.6, IC22h.6, IC23a.6, IC23b.6, IC23c.6, IC23d.6, IC23e.6, IC23f.6, IC23g.6, IC23h.6, IC24a.6, IC24b.6, IC24c.6, IC24d.6, IC24e.6, IC24f.6, IC24g.6, IC24h.6, IC25a.6, IC25b.6, IC25c.6, IC25d.6, IC25e.6, IC25f.6, IC25g.6, IC25h.6, IC26a.6, IC26b.6, IC26c.6, IC26d.6, IC26e.6, IC26f.6, IC26g.6, IC26h.6
MEM_BA4: IC15.11, IC18.4, IC19.4, IC20.4, IC21.4, IC22a.7, IC22b.7, IC22c.7, IC22d.7, IC22e.7, IC22f.7, IC22g.7, IC22h.7, IC23a.7, IC23b.7, IC23c.7, IC23d.7, IC23e.7, IC23f.7, IC23g.7, IC23h.7, IC24a.7, IC24b.7, IC24c.7, IC24d.7, IC24e.7, IC24f.7, IC24g.7, IC24h.7, IC25a.7, IC25b.7, IC25c.7, IC25d.7, IC25e.7, IC25f.7, IC25g.7, IC25h.7, IC26a.7, IC26b.7, IC26c.7, IC26d.7, IC26e.7, IC26f.7, IC26g.7, IC26h.7
MEM_BA5: IC15.13, IC18.3, IC19.3, IC20.3, IC21.3, IC22a.2, IC22b.2, IC22c.2, IC22d.2, IC22e.2, IC22f.2, IC22g.2, IC22h.2, IC23a.2, IC23b.2, IC23c.2, IC23d.2, IC23e.2, IC23f.2, IC23g.2, IC23h.2, IC24a.2, IC24b.2, IC24c.2, IC24d.2, IC24e.2, IC24f.2, IC24g.2, IC24h.2, IC25a.2, IC25b.2, IC25c.2, IC25d.2, IC25e.2, IC25f.2, IC25g.2, IC25h.2, IC26a.2, IC26b.2, IC26c.2, IC26d.2, IC26e.2, IC26f.2, IC26g.2, IC26h.2
MEM_BA6: IC16.3, IC18.2, IC19.2, IC20.2, IC21.2, IC22a.1, IC22b.1, IC22c.1, IC22d.1, IC22e.1, IC22f.1, IC22g.1, IC22h.1, IC23a.1, IC23b.1, IC23c.1, IC23d.1, IC23e.1, IC23f.1, IC23g.1, IC23h.1, IC24a.1, IC24b.1, IC24c.1, IC24d.1, IC24e.1, IC24f.1, IC24g.1, IC24h.1, IC25a.1, IC25b.1, IC25c.1, IC25d.1, IC25e.1, IC25f.1, IC25g.1, IC25h.1, IC26a.1, IC26b.1, IC26c.1, IC26d.1, IC26e.1, IC26f.1, IC26g.1, IC26h.1
MEM_BA7: IC16.5, IC18.1, IC19.1, IC20.1, IC21.1, IC22a.16, IC22b.16, IC22c.16, IC22d.16, IC22e.16, IC22f.16, IC22g.16, IC22h.16, IC23a.16, IC23b.16, IC23c.16, IC23d.16, IC23e.16, IC23f.16, IC23g.16, IC23h.16, IC24a.16, IC24b.16, IC24c.16, IC24d.16, IC24e.16, IC24f.16, IC24g.16, IC24h.16, IC25a.16, IC25b.16, IC25c.16, IC25d.16, IC25e.16, IC25f.16, IC25g.16, IC25h.16, IC26a.16, IC26b.16, IC26c.16, IC26d.16, IC26e.16, IC26f.16, IC26g.16, IC26h.16
MEM_BA8: IC16.7, IC18.23, IC19.23, IC20.23, IC21.23, IC22a.15, IC22b.15, IC22c.15, IC22d.15, IC22e.15, IC22f.15, IC22g.15, IC22h.15, IC23a.15, IC23b.15, IC23c.15, IC23d.15, IC23e.15, IC23f.15, IC23g.15, IC23h.15, IC24a.15, IC24b.15, IC24c.15, IC24d.15, IC24e.15, IC24f.15, IC24g.15, IC24h.15, IC25a.15, IC25b.15, IC25c.15, IC25d.15, IC25e.15, IC25f.15, IC25g.15, IC25h.15, IC26a.15, IC26b.15, IC26c.15, IC26d.15, IC26e.15, IC26f.15, IC26g.15, IC26h.15
MEM_BA9: IC16.9, IC18.22, IC19.22, IC20.22, IC21.22, IC22a.14, IC22b.14, IC22c.14, IC22d.14, IC22e.14, IC22f.14, IC22g.14, IC22h.14, IC23a.14, IC23b.14, IC23c.14, IC23d.14, IC23e.14, IC23f.14, IC23g.14, IC23h.14, IC24a.14, IC24b.14, IC24c.14, IC24d.14, IC24e.14, IC24f.14, IC24g.14, IC24h.14, IC25a.14, IC25b.14, IC25c.14, IC25d.14, IC25e.14, IC25f.14, IC25g.14, IC25h.14, IC26a.14, IC26b.14, IC26c.14, IC26d.14, IC26e.14, IC26f.14, IC26g.14, IC26h.14
MEM_CS0_N: IC17.15, IC18.20
MEM_CS1_N: IC17.14, IC19.20
MEM_CS2_N: IC17.13, IC20.20
MEM_CS3_N: IC17.12, LK1.1, LK2.1
MEM_CS3_RAM_N: IC22a.13, IC22b.13, IC22c.13, IC22d.13, IC22e.13, IC22f.13, IC22g.13, IC22h.13, LK2.2
MEM_CS3_ROM_N: IC21.20, LK1.2
MEM_CS4_N: IC17.11, IC23a.13, IC23b.13, IC23c.13, IC23d.13, IC23e.13, IC23f.13, IC23g.13, IC23h.13
MEM_CS5_N: IC17.10, IC24a.13, IC24b.13, IC24c.13, IC24d.13, IC24e.13, IC24f.13, IC24g.13, IC24h.13
MEM_CS6_N: IC17.9, IC25a.13, IC25b.13, IC25c.13, IC25d.13, IC25e.13, IC25f.13, IC25g.13, IC25h.13
MEM_CS7_N: IC17.7, IC26a.13, IC26b.13, IC26c.13, IC26d.13, IC26e.13, IC26f.13, IC26g.13, IC26h.13
MEM_D0: IC18.9, IC19.9, IC20.9, IC21.9, IC22h.12, IC23h.12, IC24h.12, IC25h.12, IC26h.12, IC27.2
MEM_D1: IC18.10, IC19.10, IC20.10, IC21.10, IC22g.12, IC23g.12, IC24g.12, IC25g.12, IC26g.12, IC27.4
MEM_D2: IC18.11, IC19.11, IC20.11, IC21.11, IC22f.12, IC23f.12, IC24f.12, IC25f.12, IC26f.12, IC27.6
MEM_D3: IC18.13, IC19.13, IC20.13, IC21.13, IC22e.12, IC23e.12, IC24e.12, IC25e.12, IC26e.12, IC27.8
MEM_D4: IC18.14, IC19.14, IC20.14, IC21.14, IC22d.12, IC23d.12, IC24d.12, IC25d.12, IC26d.12, IC27.12
MEM_D5: IC18.15, IC19.15, IC20.15, IC21.15, IC22c.12, IC23c.12, IC24c.12, IC25c.12, IC26c.12, IC27.14
MEM_D6: IC18.16, IC19.16, IC20.16, IC21.16, IC22b.12, IC23b.12, IC24b.12, IC25b.12, IC26b.12, IC27.16
MEM_D7: IC18.17, IC19.17, IC20.17, IC21.17, IC22a.12, IC23a.12, IC24a.12, IC25a.12, IC26a.12, IC27.18
MEM_MREQ_N: IC17.4, IC27.19, J1.39, LK3.2
MM57109_CLK: IC6.7, IC46.12
MREQ_N: IC10.11, IC31.11, IC31.12, J1.35, LK3.1
NMI_N: IC1.17, IC14.4, J1.44
PSU_3055_B: J_2N3055.B, PSU_R2.1, TR9.2
PSU_PASS_C: J_2N3055.C, PSU_R1.1, R40.2, TR9.3
PSU_REG5_IN: IC56.1, PSU_C1.1, PSU_D1.1, PSU_R1.2, TR9.1
PSU_S1_A: D1.2, J_TRANSFORMER.S1_A
PSU_S1_B: D2.2, J_TRANSFORMER.S1_B
PSU_S2_A: D4.2, D6.1, J_TRANSFORMER.S2_A
PSU_S2_B: D5.2, D7.1, J_TRANSFORMER.S2_B
PSU_S3_A: D8.2, D10.1, J_TRANSFORMER.S3_A
PSU_S3_B: D9.2, D11.1, J_TRANSFORMER.S3_B
PSU_SENSE: PSU_D1.2, R41.2
RD_N: IC3.5, IC9.1, IC9.11, IC10.1, IC27.1, J1.33
RESET_N: C_CPU3.1, IC1.26, J1.45, R_CPU4.1, SW43.1
RFSH_N: IC1.28, J1.38
SYNC: IC31.8, IC31.9, IC32.6, J_VIDEO.SYNC
SYNC_N: IC31.10, J_VIDEO.SYNC_N
TAPE_BUF_B: TAPE_R13.2, TR8.2
TAPE_IN: J_TAPE.IN, TAPE_C4.2
TAPE_MONO_C: IC52.1, TAPE_C5.2
TAPE_MONO_Q: IC51.9, IC52.6
TAPE_MONO_RC: IC52.2, TAPE_C5.1, TAPE_R15.2
TAPE_MV_B1: TAPE_C3.1, TAPE_R1.2, TAPE_R2.1, TAPE_TR1.2
TAPE_MV_B2: TAPE_C2.2, TAPE_R3.2, TAPE_R4.1, TAPE_TR2.2
TAPE_MV_C1: TAPE_C2.1, TAPE_TR1.3, VR2.3
TAPE_MV_C2: TAPE_C3.2, TAPE_R5.2, TAPE_TR2.3
TAPE_OUT: J_TAPE.OUT, TAPE_C1.2
TAPE_RXD: IC51.13, IC53.2
TAPE_RX_BIAS: TAPE_C4.1, TAPE_R6.2, TAPE_R7.1, TAPE_TR3.2
TAPE_SQ: IC51.11, IC52.4, TAPE_R14.1, TR8.3
TAPE_ST_B2: TAPE_R9.2, TAPE_R10.1, TAPE_TR4.2
TAPE_ST_C1: TAPE_R8.2, TAPE_R9.1, TAPE_TR3.3
TAPE_ST_C2: TAPE_R12.2, TAPE_R13.1, TAPE_TR4.3
TAPE_ST_E: TAPE_R11.1, TAPE_TR3.1, TAPE_TR4.1
TAPE_TXQ: IC51.1, TAPE_R2.2, TAPE_R4.2
TAPE_VR2_W: TAPE_C1.1, VR2.2
VDU_250K: IC30.12, IC48.14
VDU_B0: IC38.9, IC40.3
VDU_B1: IC38.8, IC40.6
VDU_B2: IC38.11, IC39.1, IC40.10
VDU_B3: IC39.9, IC40.13
VDU_B4: IC39.8, IC41.3
VDU_B5: IC39.11, IC41.6
VDU_B6: IC29.9, IC35.14, IC41.10
VDU_B7: IC35.1, IC35.12, IC41.13
VDU_B8: IC35.9, IC42.3
VDU_B9: IC35.8, IC42.6
VDU_B10: IC35.11, IC36.4, IC42.10
VDU_CG_CE: IC47.11, LINK_VDU4.2
VDU_CG_O1: IC45.13, IC47.4
VDU_CG_O2: IC45.14, IC47.5
VDU_CG_O3: IC45.3, IC47.6
VDU_CG_O4: IC45.4, IC47.7
VDU_CG_O5: IC45.5, IC47.8
VDU_CHR_DEC: IC32.9, IC33.6
VDU_CHR_QB: IC33.5, IC37.11
VDU_CHR_QC: IC33.4, IC37.9
VDU_CHR_QD: IC33.2, IC37.8
VDU_CLK4M: IC29.12, IC30.1, LINK_VDU3.1
VDU_DISP_RESET: C_VDU4.1, IC31.4, IC32.2, IC33.9, IC37.6, IC38.2, IC38.3, IC39.2, IC39.3
VDU_DOTCLK: IC28.6, IC29.14, IC32.10, IC37.1, IC45.2, LINK_VDU3.3
VDU_HSYNC_DEC: IC31.1, IC32.1
VDU_HSYNC_N: IC32.3, IC32.4
VDU_H_QA: IC28.9, IC48.1, IC48.12
VDU_H_QA_N: IC28.8, IC31.2
VDU_H_QB: IC31.3, IC48.9
VDU_H_QC: IC31.5, IC48.8
VDU_H_QD: IC31.6, IC34.14, IC48.11
VDU_IC30_QD: IC30.11, IC30.14
VDU_IC46_CLKIN: IC46.1, LINK_VDU3.2
VDU_IC46_QD: IC46.11, IC46.14
VDU_LOAD_N: IC32.8, IC38.1, IC45.1
VDU_MA0: IC40.4, IC43a.8, IC43b.8, IC43c.8, IC43d.8, IC43e.8, IC43f.8, IC43g.8, IC44a.8, IC44b.8, IC44c.8, IC44d.8, IC44e.8, IC44f.8, IC44g.8
VDU_MA1: IC40.7, IC43a.4, IC43b.4, IC43c.4, IC43d.4, IC43e.4, IC43f.4, IC43g.4, IC44a.4, IC44b.4, IC44c.4, IC44d.4, IC44e.4, IC44f.4, IC44g.4
VDU_MA2: IC40.9, IC43a.5, IC43b.5, IC43c.5, IC43d.5, IC43e.5, IC43f.5, IC43g.5, IC44a.5, IC44b.5, IC44c.5, IC44d.5, IC44e.5, IC44f.5, IC44g.5
VDU_MA3: IC40.12, IC43a.6, IC43b.6, IC43c.6, IC43d.6, IC43e.6, IC43f.6, IC43g.6, IC44a.6, IC44b.6, IC44c.6, IC44d.6, IC44e.6, IC44f.6, IC44g.6
VDU_MA4: IC41.4, IC43a.7, IC43b.7, IC43c.7, IC43d.7, IC43e.7, IC43f.7, IC43g.7, IC44a.7, IC44b.7, IC44c.7, IC44d.7, IC44e.7, IC44f.7, IC44g.7
VDU_MA5: IC41.7, IC43a.2, IC43b.2, IC43c.2, IC43d.2, IC43e.2, IC43f.2, IC43g.2, IC44a.2, IC44b.2, IC44c.2, IC44d.2, IC44e.2, IC44f.2, IC44g.2
VDU_MA6: IC41.9, IC43a.1, IC43b.1, IC43c.1, IC43d.1, IC43e.1, IC43f.1, IC43g.1, IC44a.1, IC44b.1, IC44c.1, IC44d.1, IC44e.1, IC44f.1, IC44g.1
VDU_MA7: IC41.12, IC43a.16, IC43b.16, IC43c.16, IC43d.16, IC43e.16, IC43f.16, IC43g.16, IC44a.16, IC44b.16, IC44c.16, IC44d.16, IC44e.16, IC44f.16, IC44g.16
VDU_MA8: IC42.4, IC43a.15, IC43b.15, IC43c.15, IC43d.15, IC43e.15, IC43f.15, IC43g.15, IC44a.15, IC44b.15, IC44c.15, IC44d.15, IC44e.15, IC44f.15, IC44g.15
VDU_MA9: IC42.7, IC43a.14, IC43b.14, IC43c.14, IC43d.14, IC43e.14, IC43f.14, IC43g.14, IC44a.14, IC44b.14, IC44c.14, IC44d.14, IC44e.14, IC44f.14, IC44g.14
VDU_MA10: IC28.13, IC42.9, IC43a.13, IC43b.13, IC43c.13, IC43d.13, IC43e.13, IC43f.13, IC43g.13
VDU_MA10_N: IC28.12, IC44a.13, IC44b.13, IC44c.13, IC44d.13, IC44e.13, IC44f.13, IC44g.13
VDU_MONO_C: C_VDU2.2, IC36.10
VDU_MONO_Q: IC33.12, IC34.2, IC34.3, IC36.6
VDU_MONO_Q_N: C_VDU3.1, IC36.1, R_VDU3.2
VDU_MONO_RC: C_VDU2.1, IC36.11, VR1.2, VR1.3
VDU_MREQ: IC31.13, IC32.12
VDU_MUX_SEL: IC32.11, IC40.1, IC41.1, IC42.1, IC49.2
VDU_OSC_IN: IC28.1, R_VDU1.1, X_VDU1.1
VDU_OSC_MID: IC28.2, IC28.3, R_VDU1.2, R_VDU2.1
VDU_OSC_OUT: C_VDU1.2, IC28.4, IC28.5, R_VDU2.2
VDU_RAM_WE_N: IC43a.3, IC43b.3, IC43c.3, IC43d.3, IC43e.3, IC43f.3, IC43g.3, IC44a.3, IC44b.3, IC44c.3, IC44d.3, IC44e.3, IC44f.3, IC44g.3, IC49.4
VDU_RD0: IC43a.12, IC44a.12, IC47.17
VDU_RD1: IC43b.12, IC44b.12, IC47.18
VDU_RD2: IC43c.12, IC44c.12, IC47.19
VDU_RD3: IC43d.12, IC44d.12, IC47.20
VDU_RD4: IC43e.12, IC44e.12, IC47.21
VDU_RD5: IC43f.12, IC44f.12, IC47.22
VDU_RD6: IC43g.12, IC44g.12
VDU_ROW0: IC34.1, IC34.12, IC47.14
VDU_ROW1: IC34.9, IC47.15
VDU_ROW2: IC34.8, IC47.16
VDU_ROW3: IC29.1, IC34.11, LINK_VDU1.1
VDU_ROWBLANK: IC33.10, LINK_VDU1.2
VDU_SR_H: IC45.6, LINK_VDU2.1
VDU_SR_OUT_N: IC33.13, IC45.7
VDU_VIDGATE: IC28.11, IC33.8
VDU_VSYNC_TRIG: C_VDU3.2, IC32.5, R_VDU4.2
VDU_VWR: IC49.1, IC49.5, IC49.6
VDU_XTAL_C: C_VDU1.1, X_VDU1.2
VIDEO: IC28.10, J_VIDEO.VIDEO
VUNREG_5: C14.1, D1.1, D2.1, R40.1, R41.1
VUNREG_12N: C18.2, D6.2, D7.2, PSU_IC2.2, PSU_IC3.2
VUNREG_12P: C17.1, D4.1, D5.1, PSU_IC1.1
VUNREG_55: C19.1, D8.1, D9.1, PSU_R8.1
WAIT_N: IC1.24, IC1.25, J1.41, R_CPU5.1
WR_N: IC2.5, IC9.13, IC11.1, IC12.1, IC22a.3, IC22b.3, IC22c.3, IC22d.3, IC22e.3, IC22f.3, IC22g.3, IC22h.3, IC23a.3, IC23b.3, IC23c.3, IC23d.3, IC23e.3, IC23f.3, IC23g.3, IC23h.3, IC24a.3, IC24b.3, IC24c.3, IC24d.3, IC24e.3, IC24f.3, IC24g.3, IC24h.3, IC25a.3, IC25b.3, IC25c.3, IC25d.3, IC25e.3, IC25f.3, IC25g.3, IC25h.3, IC26a.3, IC26b.3, IC26c.3, IC26d.3, IC26e.3, IC26f.3, IC26g.3, IC26h.3, IC49.3, J1.34

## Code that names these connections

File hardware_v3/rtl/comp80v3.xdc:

# COMP80 v3 pins: made by tools/design.py from the board's tables; don't edit.
# Every bank's VCCO is 3.3 V. HDMI uses TMDS_33, which drives the display's
# 50 ohm terminations directly.

set_property CFGBVS VCCO [current_design]
set_property CONFIG_VOLTAGE 3.3 [current_design]
set_property BITSTREAM.CONFIG.SPI_BUSWIDTH 4 [current_design]
set_property BITSTREAM.CONFIG.CONFIGRATE 33 [current_design]
set_property BITSTREAM.GENERAL.COMPRESS TRUE [current_design]

set_property -dict {PACKAGE_PIN B17 IOSTANDARD LVCMOS33} [get_ports {clk100}]   ;# 100 MHz oscillator (bank 16 SRCC)
set_property -dict {PACKAGE_PIN A13 IOSTANDARD TMDS_33} [get_ports {tmds_p[0]}]   ;# HDMI data 0+ (blue)
set_property -dict {PACKAGE_PIN A14 IOSTANDARD TMDS_33} [get_ports {tmds_n[0]}]   ;# HDMI data 0-
set_property -dict {PACKAGE_PIN A15 IOSTANDARD TMDS_33} [get_ports {tmds_p[1]}]   ;# HDMI data 1+ (green)
set_property -dict {PACKAGE_PIN A16 IOSTANDARD TMDS_33} [get_ports {tmds_n[1]}]   ;# HDMI data 1-
set_property -dict {PACKAGE_PIN B15 IOSTANDARD TMDS_33} [get_ports {tmds_p[2]}]   ;# HDMI data 2+ (red)
set_property -dict {PACKAGE_PIN B16 IOSTANDARD TMDS_33} [get_ports {tmds_n[2]}]   ;# HDMI data 2-
set_property -dict {PACKAGE_PIN A18 IOSTANDARD TMDS_33} [get_ports {tmds_p[3]}]   ;# HDMI clock+
set_property -dict {PACKAGE_PIN A19 IOSTANDARD TMDS_33} [get_ports {tmds_n[3]}]   ;# HDMI clock-
set_property -dict {PACKAGE_PIN B20 IOSTANDARD LVCMOS33} [get_ports {usb_dp}]   ;# Keyboard USB D+
set_property -dict {PACKAGE_PIN A20 IOSTANDARD LVCMOS33} [get_ports {usb_dm}]   ;# Keyboard USB D-
set_property -dict {PACKAGE_PIN J22 IOSTANDARD LVCMOS33} [get_ports {sd_sck}]   ;# microSD CLK
set_property -dict {PACKAGE_PIN H22 IOSTANDARD LVCMOS33} [get_ports {sd_mosi}]   ;# microSD CMD
set_property -dict {PACKAGE_PIN K22 IOSTANDARD LVCMOS33} [get_ports {sd_miso}]   ;# microSD DAT0
set_property -dict {PACKAGE_PIN M22 IOSTANDARD LVCMOS33} [get_ports {sd_cs_n}]   ;# microSD DAT3/CS
set_property -dict {PACKAGE_PIN AB10 IOSTANDARD LVCMOS33} [get_ports {uart_tx}]   ;# Serial console out
set_property -dict {PACKAGE_PIN AB11 IOSTANDARD LVCMOS33} [get_ports {led_halt}]   ;# HALT LED
set_property -dict {PACKAGE_PIN AB12 IOSTANDARD LVCMOS33} [get_ports {btn_reset_n}]   ;# RESET button (low when pressed)
set_property -dict {PACKAGE_PIN B1 IOSTANDARD LVDS_25} [get_ports {dp_aux_p}]   ;# DisplayPort AUX+ (SBU1)
set_property -dict {PACKAGE_PIN A1 IOSTANDARD LVDS_25} [get_ports {dp_aux_n}]   ;# DisplayPort AUX- (SBU2)
set_property -dict {PACKAGE_PIN C2 IOSTANDARD LVCMOS25} [get_ports {pd_scl}]   ;# FUSB302 I2C clock
set_property -dict {PACKAGE_PIN D1 IOSTANDARD LVCMOS25} [get_ports {pd_sda}]   ;# FUSB302 I2C data
set_property -dict {PACKAGE_PIN E1 IOSTANDARD LVCMOS25} [get_ports {pd_int_n}]   ;# FUSB302 interrupt
set_property -dict {PACKAGE_PIN F1 IOSTANDARD LVCMOS25} [get_ports {vbus_en}]   ;# Monitor VBUS switch on
set_property -dict {PACKAGE_PIN G1 IOSTANDARD LVCMOS25} [get_ports {vbus_flt_n}]   ;# Monitor VBUS fault
# GTP transceiver pins (bank 216) and their 135 MHz reference
set_property PACKAGE_PIN D7 [get_ports {dp_tx_p[0]}]   ;# J7 TX1+
set_property PACKAGE_PIN C7 [get_ports {dp_tx_n[0]}]   ;# J7 TX1-
set_property PACKAGE_PIN B6 [get_ports {dp_tx_p[1]}]   ;# J7 RX1+
set_property PACKAGE_PIN A6 [get_ports {dp_tx_n[1]}]   ;# J7 RX1-
set_property PACKAGE_PIN D5 [get_ports {dp_tx_p[2]}]   ;# J7 TX2+
set_property PACKAGE_PIN C5 [get_ports {dp_tx_n[2]}]   ;# J7 TX2-
set_property PACKAGE_PIN B4 [get_ports {dp_tx_p[3]}]   ;# J7 RX2+
set_property PACKAGE_PIN A4 [get_ports {dp_tx_n[3]}]   ;# J7 RX2-
set_property PACKAGE_PIN F6 [get_ports {dp_refclk_p}]   ;# 135 MHz reference+
set_property PACKAGE_PIN E6 [get_ports {dp_refclk_n}]   ;# 135 MHz reference-

create_clock -period 10.000 -name clk100 [get_ports clk100]
# the USB core, the system clock and the pixel clock only meet through synchronisers
set_clock_groups -asynchronous -group [get_clocks -of_objects [get_pins pll/CLKOUT0]] \
    -group [get_clocks -of_objects [get_pins pll/CLKOUT1]] \
    -group [get_clocks -of_objects [get_pins mmcm/CLKOUT0]]
create_clock -period 7.407 -name dp_refclk [get_ports dp_refclk_p]
# Vivado doesn't derive the GTPs' own clocks: 2.7 Gb/s over 20 bits is 135 MHz, and the
# fabric copy of the reference clocks each channel's reset controller
create_clock -period 7.407 -name dp_symbol [get_pins dp/gtp/tx0/i_gtpe2/TXOUTCLK]
create_clock -period 7.407 -name dp_gt_ref [get_pins dp/gtp/*/i_gtpe2/TXOUTCLKFABRIC]
# the DisplayPort source meets the AUX channel and the rest only through synchronisers
set_clock_groups -asynchronous -group [get_clocks dp_symbol] -group [get_clocks dp_gt_ref] \
    -group [get_clocks -include_generated_clocks clk100]
set_property PULLDOWN true [get_ports {usb_dp usb_dm}]
set_property PULLUP true [get_ports btn_reset_n]
# hamsternz's AUX channel and link management run from clk100, as on his boards
set_clock_groups -asynchronous -group [get_clocks clk100] -group [get_clocks -of_objects [get_pins pll/CLKOUT0]]

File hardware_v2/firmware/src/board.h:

// The COMP80 v2 board's pins (hardware_v2/tools/design.py, GPIO_USE, must agree).
#ifndef BOARD_H
#define BOARD_H

#define PIN_UART_TX   0     // serial console on the debug header, 115200 baud
#define PIN_UART_RX   1

#define SD_SPI        spi1
#define PIN_SD_MISO   8     // DAT0
#define PIN_SD_CS     9     // DAT3
#define PIN_SD_SCK    10    // CLK
#define PIN_SD_MOSI   11    // CMD

// HDMI on the HSTX port, GPIO12-19 = HSTX bits 0-7, through 270R each:
//   12/13 TMDS data 2 +/- (red), 14/15 data 1 (green), 16/17 data 0 (blue),
//   18/19 the TMDS clock
#define HSTX_BIT_D2   0
#define HSTX_BIT_D1   2
#define HSTX_BIT_D0   4
#define HSTX_BIT_CK   6

#define PIN_USBH_DP   20    // keyboard, PIO-USB; D- is the next pin
#define PIN_HALT_LED  25

#endif

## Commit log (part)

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2026-01-26 Initial version, gets to READY prompt, and RUN command but little else
2026-01-26 Updated build instuctions
2026-01-27 Fixup possible errors in ROM scan
2026-01-27 Fixed the error at 03b9 properly. LIST command now works
2026-01-27 Added description of the monitor commands
2026-01-27 Fixed some typos in the hardware desc. Implemented the RESET key as ESC
2026-01-27 Implemented RS (Burp) key as F2
2026-01-27 Added more documentation. Remove RS key mapping as Shift Cmd ^ works on mac for BURP mode
2026-01-28 Added dissassembly notes for monitor
2026-01-30 Fixed some ROM errors in BURP, still unable to RUN 5 on text list
2026-01-31 More annotation in the dissembly of the ROM BURP part. Loggin got MM57109 interaction added. Still resets to READY on RUN 5 of test program
2026-02-01 Added PRINT and NEXT token identification in the annotated asm
2026-02-03 Added more annotation on BURP, added more info on MM57109 operation, Still not getting past FOR statement
2026-02-04 State machine implemented for mm57109. Currently WIP. FOR test program still fails
2026-02-04 Added new comments to dissassembly
2026-02-06 OUT* instuction working, minor updates to documentation, test program runs but does not work
2026-02-06 Added logging of X Y registers
2026-02-07 Number entry working, no math functions yet
2026-02-07 Math working, reduced logging, TXF* instruction not implemented
2026-02-08 TXF* implemented as a single word instruction, loop still not breaking
2026-02-08 INV functions still not firing. Incremental number entry is being done
2026-02-08 TXF showing correct result but not being dectected in BURP
2026-02-08 Removed redundant status variable, trying to fix TXF instuction
2026-02-09 No functional changes, updated documentation and reformmated code
2026-02-09 Working BURP test program. Major milestone
2026-02-09 Added more comments to code, tried getting RDY/HOLD logic right in simulator but still not right
2026-02-12 Moved to a timer based approach for RDY on MM57109, still a problem with branch management
2026-02-12 OK TXF* instruction now working, BURP test program is working
2026-02-13 DEL 6 command doesn't reset to monitor - but doesn't work yet either. Patched 1 byte in the ROM
2026-02-14 More annotation around BURP command processing and correction of dissasembly, no functional changes
2026-02-14 In middle of annotating DEL command, all looks good so far
2026-02-14 Fixed 'DEL 6' problem, changed byte in ROM
2026-02-15 Added more annotation
2026-02-15 Added support for cassette interface
2026-02-15 Added extended gyph font
2026-02-15 Half of the graphics chars entered
2026-02-15 More grphic chars added
2026-02-16 All extended chars done
